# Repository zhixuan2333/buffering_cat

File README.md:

# Buffering Cat

Buffering Cat is a tiny USB status light built around the WCH CH32V003. Eight
LEDs form a ring around a cat face and can be controlled from the browser, the
Rust CLI, or lightweight Codex/ChatGPT activity hooks.

The repository contains the complete KiCad design, firmware, host tools, and a
WebHID controller with browser-based firmware updates.

## Repository layout

- [`buffering_cat.kicad_sch`](buffering_cat.kicad_sch) and
  [`buffering_cat.kicad_pcb`](buffering_cat.kicad_pcb): current hardware v1.1
- [`firmware/`](firmware/README.md): CH32V003 application and one-time USB HID
  bootloader
- [`host/`](host/README.md): native Rust command-line controller
- [`webhid/`](webhid/README.md): Chrome/Edge controller and firmware updater
- [`integrations/`](integrations/README.md): token-free Codex/ChatGPT activity
  hooks

Generated fabrication files, KiCad backups, editor state, build products,
dependencies, and tool caches are intentionally excluded from Git.

## Hardware revisions

| Revision | LED matrix GPIO | USB GPIO | Notes |
| --- | --- | --- | --- |
| v1.0 | `PA1/PD4/PA2` × `PD0/PC7/PC0` | `PD3=D+`, `PD2=D-` | Original 3×3 matrix; A2/C2 share a node and can ghost |
| v1.1 | `PC0/PD4/PC1/PA1` × `PC2/PA2` | `PD3=D+`, `PD2=D-`, `PD0=DPU` | Current KiCad 4×2 matrix; PD0 drives R5 (1.5 kΩ) |

On v1.0, D1 is at the left and D2–D8 continue counter-clockwise. Starting with
v1.1, D1 is at the top and D2–D8 continue counter-clockwise. Select the matching
hardware revision when building or updating; a build for the wrong revision
will drive the wrong GPIOs.

## Firmware releases

GitHub Actions builds application images for both v1.0 and v1.1, the common
USB bootloader, and native Rust controller binaries for Linux, macOS, and
Windows on both x86_64 and ARM64.

- A push to `main` that changes firmware creates a prerelease whose tag is the
  first eight characters of the Git commit hash. GitHub rejects tag names made
  of exactly 40 hexadecimal characters, so a full SHA cannot be used directly.
- **Run workflow → Firmware release** accepts a manual `vX.Y.Z` version and
  publishes it as the latest stable release.
- Every release includes both `.bin` files, the one-time bootloader, six native
  CLI archives, `firmware-manifest.json`, and `SHA256SUMS`.

The application embeds the release version, Git hash, hardware revision, and
HID protocol version. `buffering-cat status` and the web controller expose the
machine-readable hardware/hash fields.

## Firmware updates

Install `buffering-cat-usb-bootloader.bin` once with WCH-Link. After that, open
the WebHID site in current Chrome or Edge, select the hardware revision and
release, reboot the device to updater mode, and install directly in the
browser. A local `.bin` can be selected when testing an unreleased build.
On connection, the site automatically detects the hardware revision and
firmware commit. It also resolves and selects the matching `vX.Y.Z` GitHub
Release when one exists.

The Rust CLI remains available as a recovery/update path:

```sh
buffering-cat bootloader
buffering-cat flash-usb buffering-cat-v1.1-v1.2.3.bin
```

The web controller is a serverless static export intended for self-deployment
to Cloudflare Pages. Use `webhid` as the project root and `out` as the build
output directory; no OpenAI/ChatGPT hosting integration is included.

## Local checks

```sh
make -C firmware HARDWARE_REV=10
make -C firmware clean
make -C firmware HARDWARE_REV=11
cargo test --manifest-path host/Cargo.toml
npm --prefix webhid test
```

The firmware Makefile expects sibling `ch32fun` and `rv003usb` checkouts by
default; see [`firmware/README.md`](firmware/README.md) for path overrides.

## Links

[Watch or download the video (MP4)](assets/project-announcement.mp4) · [View the original post on X](https://x.com/zhixuan2333/status/2087470282600771743)

## License

MIT. See [`LICENSE`](LICENSE).

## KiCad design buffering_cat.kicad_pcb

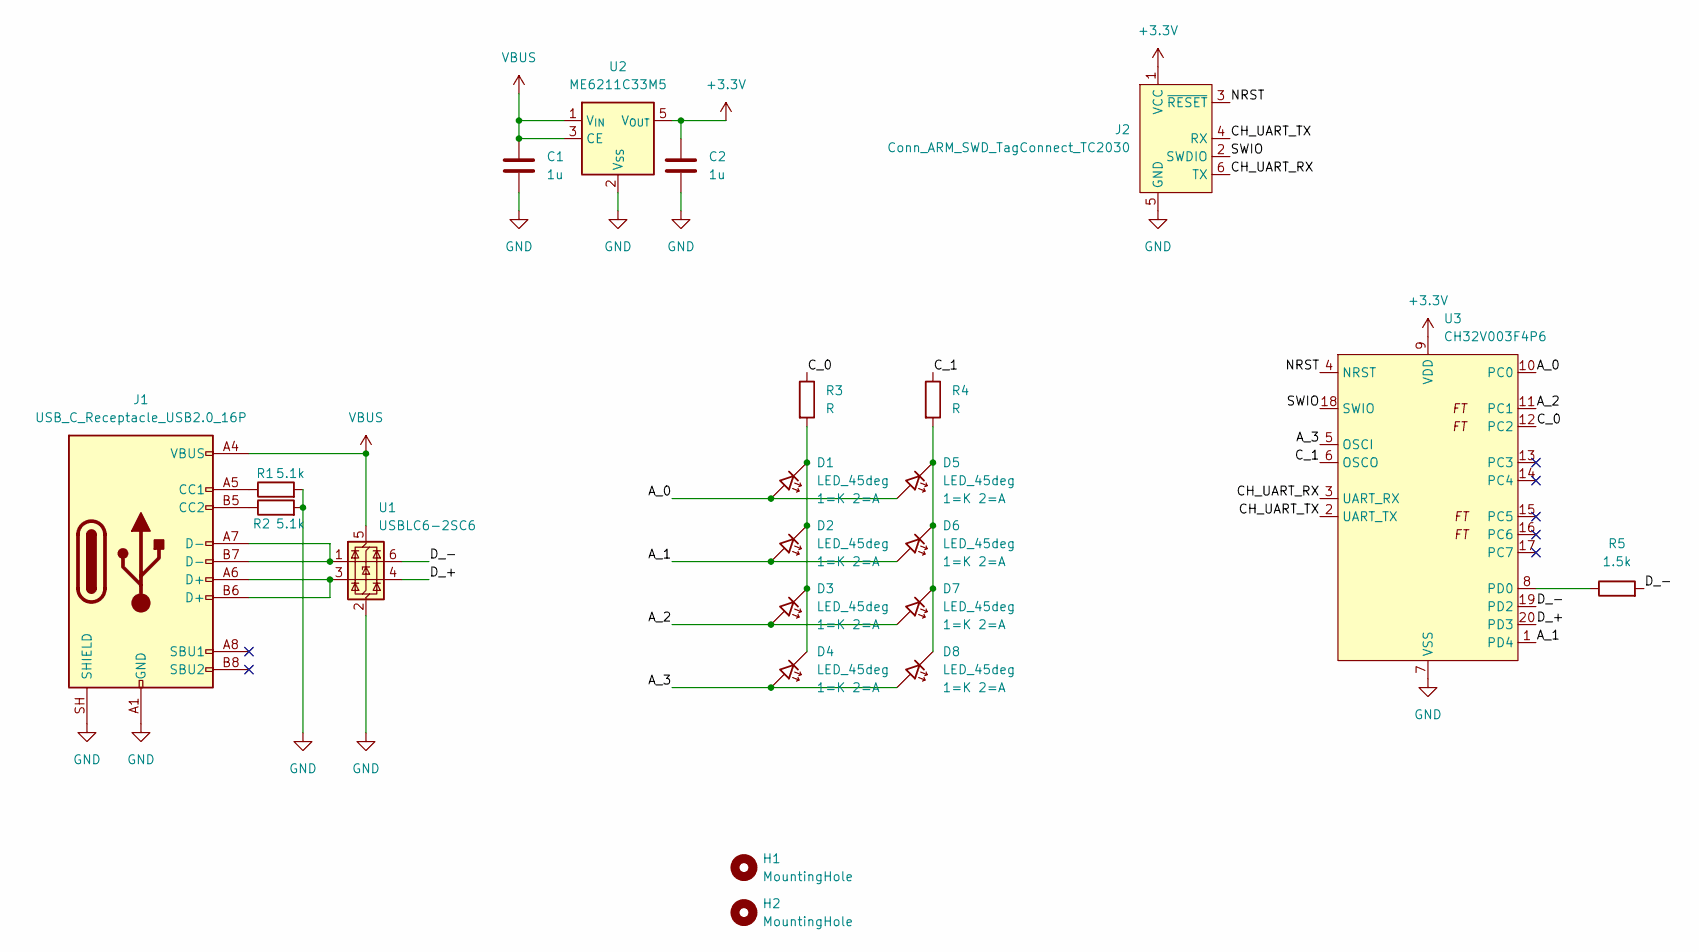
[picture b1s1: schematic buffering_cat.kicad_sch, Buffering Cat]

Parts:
C1, C2: 1u; C_0603_1608Metric
D1, D2, D3, D4, D5, D6, D7, D8: LED_45deg; LED_0603_1608Metric_Pad1.05x0.95mm_HandSolder
H1, H2: MountingHole; MountingHole_3.2mm_M3
J1: USB_C_Receptacle_USB2.0_16P; USB_C_Receptacle_Palconn_UTC16-G
J2: Conn_ARM_SWD_TagConnect_TC2030; Tag-Connect_TC2030-IDC-FP_2x03_P1.27mm_Vertical
R1, R2: 5.1k; R_0603_1608Metric
R3, R4: R; R_0603_1608Metric_Pad0.98x0.95mm_HandSolder
R5: 1.5k; R_0603_1608Metric
U1: USBLC6-2SC6; SOT-23-6
U2: ME6211C33M5; SOT-23-5
U3: CH32V003F4P6; TSSOP-20_4.4x6.5mm_P0.65mm

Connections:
+3.3V: C2.1, J2.1 (VCC), U2.5 (V_{OUT}), U3.9 (VDD)
/A_0: D1.2 (A), D5.2 (A), U3.10 (PC0)
/A_1: D2.2 (A), D6.2 (A), U3.1 (PD4)
/A_2: D3.2 (A), D7.2 (A), U3.11 (PC1)
/A_3: D4.2 (A), D8.2 (A), U3.5 (OSCI)
/CH_UART_RX: J2.6 (TX), U3.3 (UART_RX)
/CH_UART_TX: J2.4 (RX), U3.2 (UART_TX)
/C_0: R3.1, U3.12 (PC2)
/C_1: R4.1, U3.6 (OSCO)
/D_+: U1.4 (I/O2), U3.20 (PD3)
/D_-: R5.2, U1.6 (I/O1), U3.19 (PD2)
/NRST: J2.3 (~RESET), U3.4 (NRST)
/SWIO: J2.2 (SWDIO), U3.18 (SWIO)
GND: C1.2, C2.2, J1.A1 (GND), J1.A12 (GND), J1.B1 (GND), J1.B12 (GND), J1.SH (SHIELD), J2.5 (GND), R1.2, R2.2, U1.2 (GND), U2.2 (V_{SS}), U3.7 (VSS)
unnamed: D1.1 (K), D2.1 (K), D3.1 (K), D4.1 (K), R3.2
unnamed: D5.1 (K), D6.1 (K), D7.1 (K), D8.1 (K), R4.2
unnamed: J1.A5 (CC1), R1.1
unnamed: J1.B5 (CC2), R2.1
unnamed: J1.A6 (D+), J1.B6 (D+), U1.3 (I/O2)
unnamed: J1.A7 (D-), J1.B7 (D-), U1.1 (I/O1)
unnamed: R5.1, U3.8 (PD0)
VBUS: C1.1, J1.A4 (VBUS), J1.A9 (VBUS), J1.B4 (VBUS), J1.B9 (VBUS), U1.5 (VBUS), U2.1 (V_{IN}), U2.3 (CE)

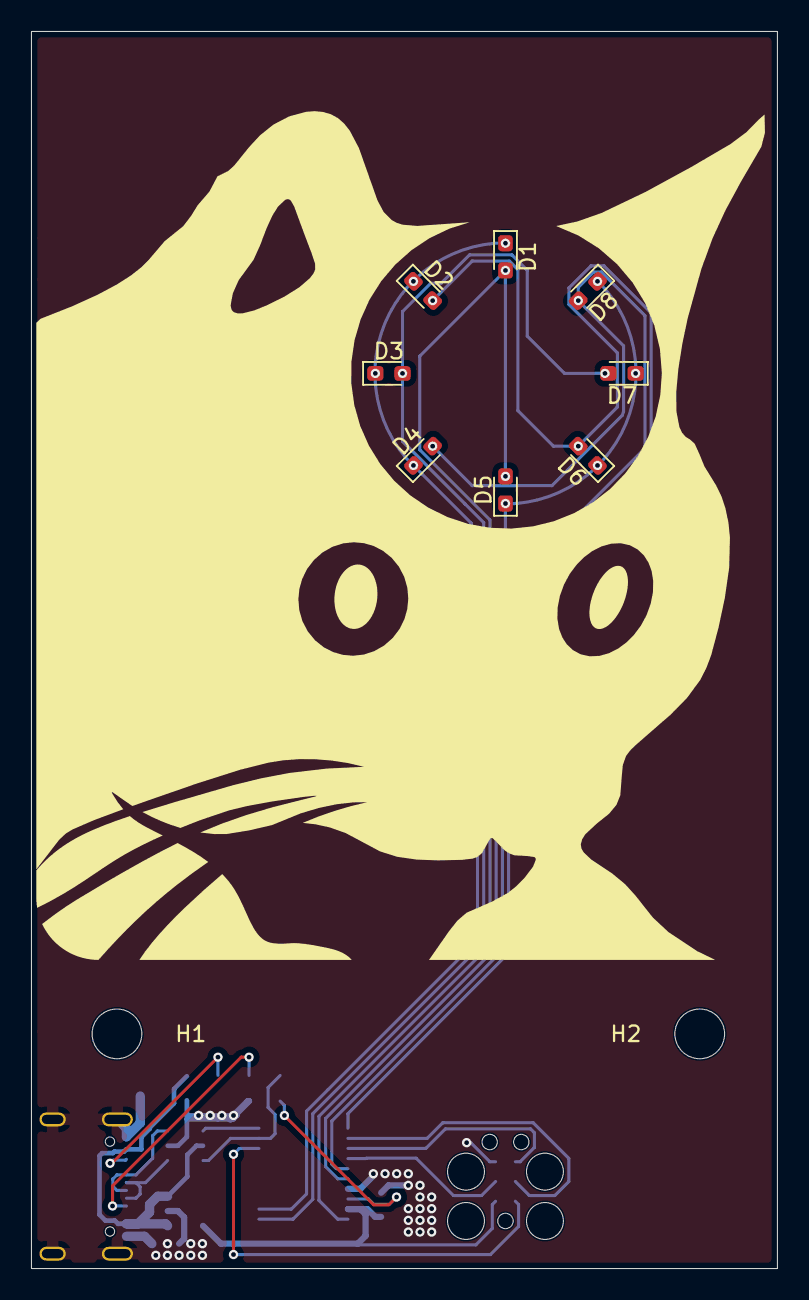
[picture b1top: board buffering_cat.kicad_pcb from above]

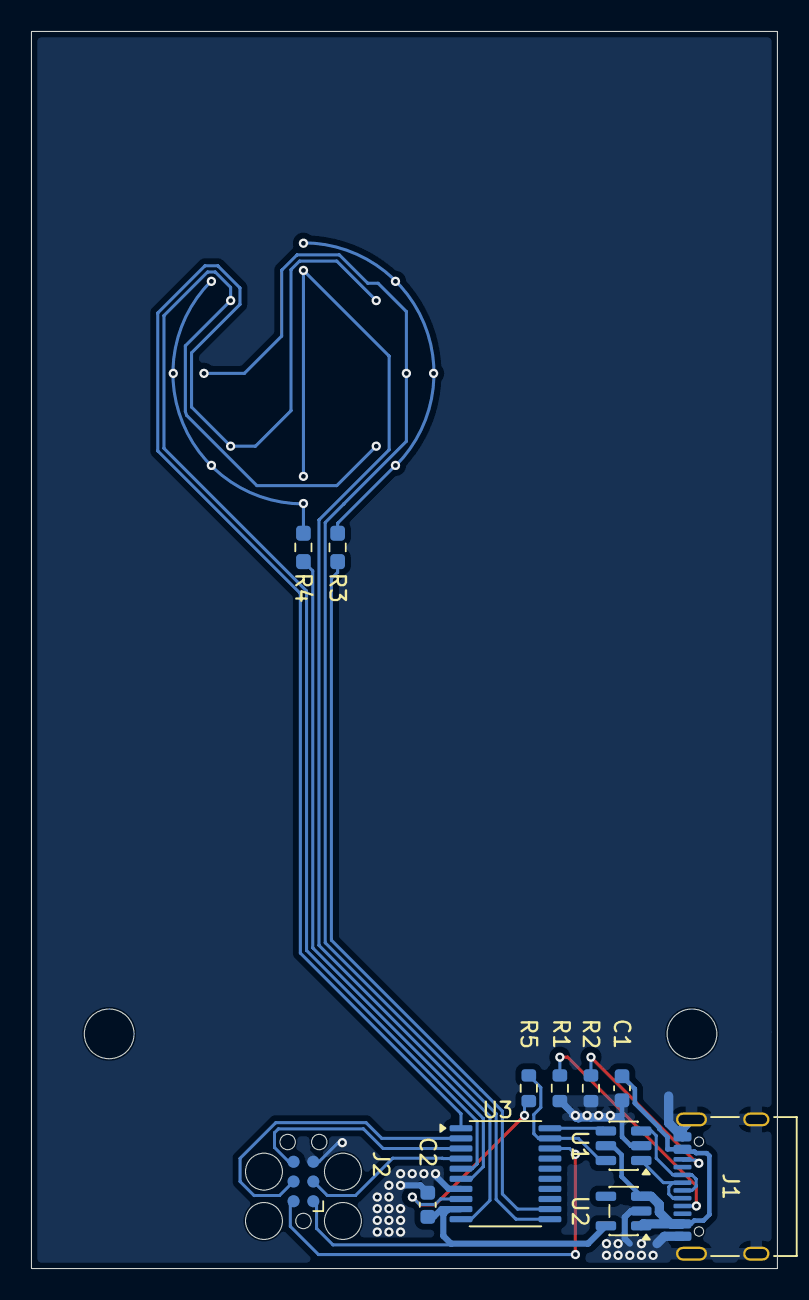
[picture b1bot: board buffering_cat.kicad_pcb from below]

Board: 2 copper layers, 48.0 x 79.6 mm, 22 parts (12 on the bottom side), 22 nets.

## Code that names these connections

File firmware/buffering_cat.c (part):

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#if BUFFERING_CAT_HARDWARE_REV == 10
#define FIRMWARE_HARDWARE_ID 0x10
#define A0 PA1
#define A1 PD4
#define A2 PA2
#define C0 PD0
#define C1 PC7
#define C2 PC0
#elif BUFFERING_CAT_HARDWARE_REV == 11
#define FIRMWARE_HARDWARE_ID 0x11
/* KiCad v1.1: four independent anodes by two cathode rows. */
#define A0 PC0
#define A1 PD4
#define A2 PC1
#define A3 PA1
#define C0 PC2
#define C1 PA2
#else
#error "BUFFERING_CAT_HARDWARE_REV must be 10 (v1.0) or 11 (v1.1)"
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	leds_off();

	/* Force a disconnect pulse when the mandatory external D- pull-up exists. */
	funDigitalWrite(PD2, FUN_LOW);
	funPinMode(PD2, GPIO_Speed_10MHz | GPIO_CNF_OUT_PP);
	Delay_Ms(20);
	funPinMode(PD2, GPIO_CNF_IN_FLOATING);

	usb_setup();
	next_led_slot_tick = SysTick->CNT + LED_SLOT_TICKS;
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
